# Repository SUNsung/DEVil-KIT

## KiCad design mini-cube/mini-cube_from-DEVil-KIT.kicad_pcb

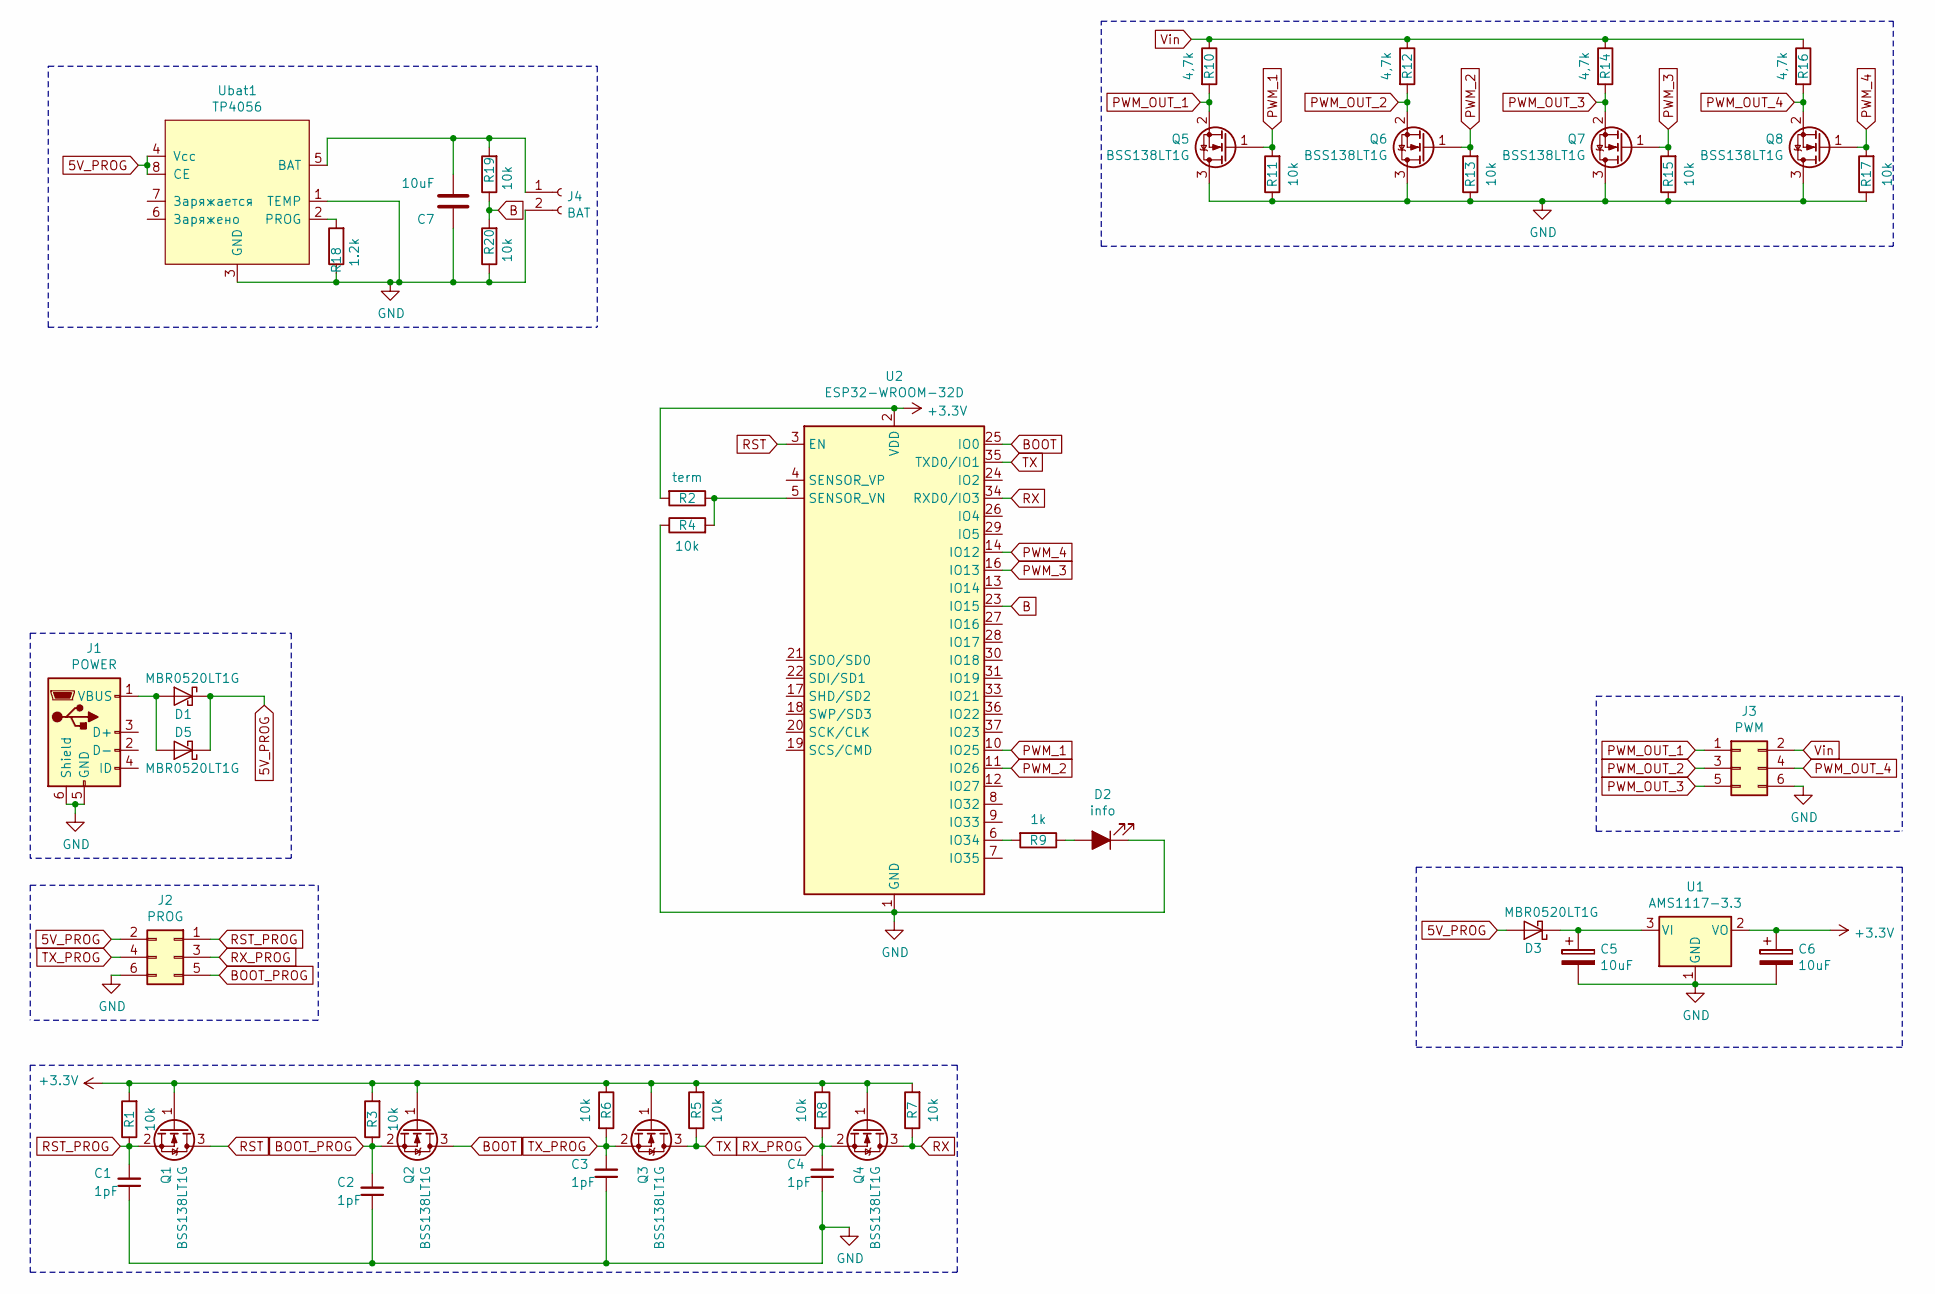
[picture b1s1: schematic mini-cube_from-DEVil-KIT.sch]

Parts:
C1, C2, C3, C4: 1pF; C_0603_1608Metric_Pad1.05x0.95mm_HandSolder
C5, C6: 10uF; CP_EIA-3528-21_Kemet-B_Pad1.50x2.35mm_HandSolder
C7: 10uF; C_0805_2012Metric
D1, D3, D5: MBR0520LT1G; D_SOD-123F
D2: info; D_0805_2012Metric_Castellated
J1: POWER; USB_Mini-B_Lumberg_2486_01_Horizontal
J2: PROG; IDC-Header_2x03_P2.54mm_Horizontal
J3: PWM; IDC-Header_2x03_P2.54mm_Horizontal
J4: BAT; SolderWirePad_1x02_P3.81mm_Drill0.8mm
Q1, Q2, Q3, Q4, Q5, Q6, Q7, Q8: BSS138LT1G; SOT-323_SC-70
R1, R3, R5, R6, R7, R8, R11, R13, R15, R17: 10k; R_0603_1608Metric_Pad1.05x0.95mm_HandSolder
R2: term; R_0805_2012Metric
R4, R19, R20: 10k; R_0805_2012Metric
R9: 1k; R_0805_2012Metric
R10, R12, R14, R16: 4,7k; R_0603_1608Metric_Pad1.05x0.95mm_HandSolder
R18: 1.2k; R_0805_2012Metric
U1: AMS1117-3.3; SOT-223-3_TabPin2
U2: ESP32-WROOM-32D; modul_ESP32S
Ubat1: TP4056; HSOP-8-1EP_3.9x4.9mm_P1.27mm_EP2.41x3.1mm

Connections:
5V_PROG: D1.1 (K), D3.2 (A), D5.1 (K), J2.2, Ubat1.4 (Vcc), Ubat1.8 (CE)
+3V3: C6.1, Q1.1 (G), Q2.1 (G), Q3.1 (G), Q4.1 (G), R1.2, R2.2, R3.2, R5.2, R6.1, R7.2, R8.1, U1.2 (VO), U2.2 (VDD)
B: R19.1, R20.2, U2.23 (IO15)
BOOT: Q2.3 (D), U2.25 (IO0)
BOOT_PROG: C2.2, J2.5, Q2.2 (S), R3.1
GND: C1.1, C2.1, C3.1, C4.1, C5.2, C6.2, C7.2, D2.1 (K), J1.5 (GND), J1.6 (Shield), J2.6, J3.6, J4.2, Q5.3 (D), Q6.3 (D), Q7.3 (D), Q8.3 (D), R4.1, R11.1, R13.1, R15.1, R17.1, R18.1, R20.1, U1.1 (GND), U2.1 (GND), U2.15 (GND), U2.38 (GND), Ubat1.1 (TEMP), Ubat1.3 (GND)
unnamed: C5.1, D3.1 (K), U1.3 (VI)
unnamed: C7.1, J4.1, R19.2, Ubat1.5 (BAT)
unnamed: D1.2 (A), D5.2 (A), J1.1 (VBUS)
unnamed: D2.2 (A), R9.1
unnamed: R2.1, R4.2, U2.5 (SENSOR_VN)
unnamed: R9.2, U2.6 (IO34)
unnamed: R18.2, Ubat1.2 (PROG)
PWM_1: Q5.1 (G), R11.2, U2.10 (IO25)
PWM_2: Q6.1 (G), R13.2, U2.11 (IO26)
PWM_3: Q7.1 (G), R15.2, U2.16 (IO13)
PWM_4: Q8.1 (G), R17.2, U2.14 (IO12)
PWM_OUT_1: J3.1, Q5.2 (S), R10.2
PWM_OUT_2: J3.3, Q6.2 (S), R12.2
PWM_OUT_3: J3.5, Q7.2 (S), R14.2
PWM_OUT_4: J3.4, Q8.2 (S), R16.2
RST: Q1.3 (D), U2.3 (EN)
RST_PROG: C1.2, J2.1, Q1.2 (S), R1.1
RX: Q4.3 (D), R7.1, U2.34 (RXD0/IO3)
RX_PROG: C4.2, J2.3, Q4.2 (S), R8.2
TX: Q3.3 (D), R5.1, U2.35 (TXD0/IO1)
TX_PROG: C3.2, J2.4, Q3.2 (S), R6.2
Vin: J3.2, R10.1, R12.1, R14.1, R16.1

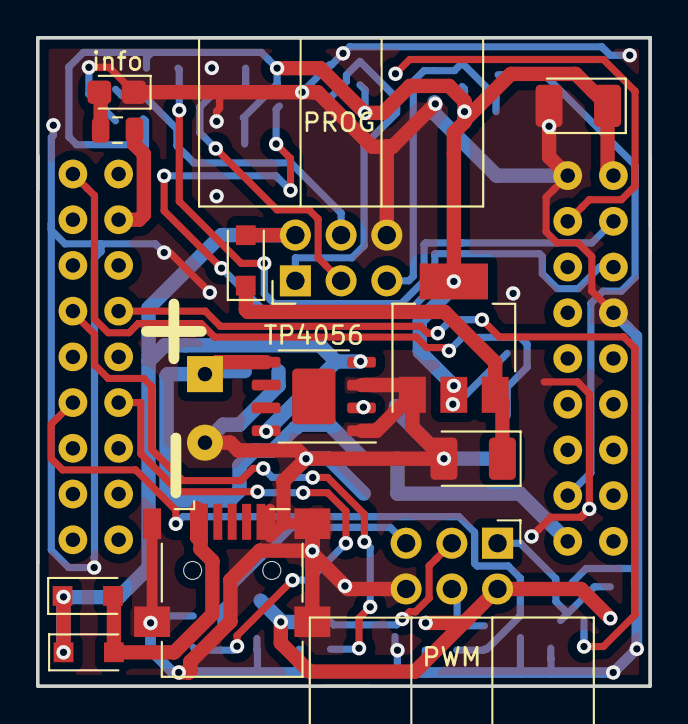
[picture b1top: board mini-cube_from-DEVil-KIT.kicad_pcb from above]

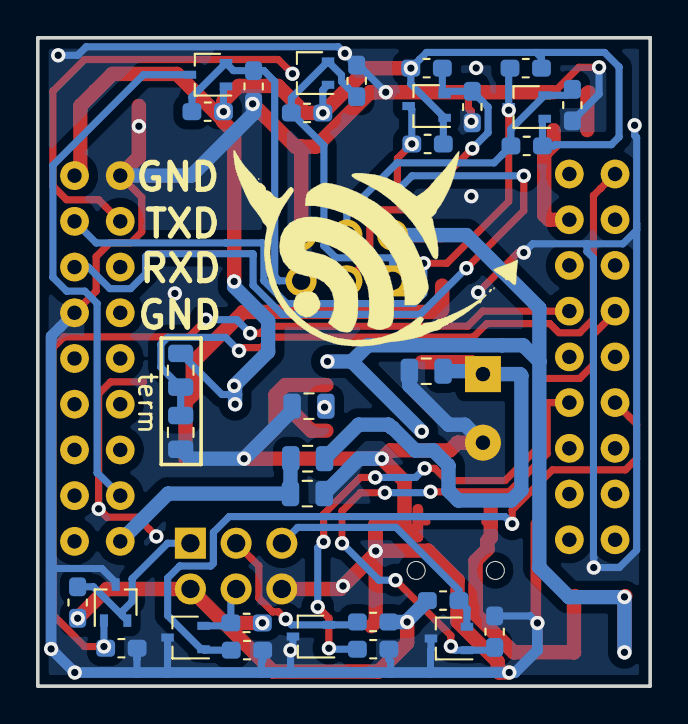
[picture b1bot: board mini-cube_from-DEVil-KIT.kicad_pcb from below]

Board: 2 copper layers, 34.0 x 36.0 mm, 46 parts (33 on the bottom side), 28 nets.

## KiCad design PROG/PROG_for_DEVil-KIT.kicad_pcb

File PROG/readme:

The module programmer is worn on the USB-UART CP2104 CP2102 adapter

6\май\2019 - Собрал. Нежизнеспособно. Зашита пробивается на раз. Греется как утюг. Резюмируя - при необходимости программатор собирать с нуля под задачу.

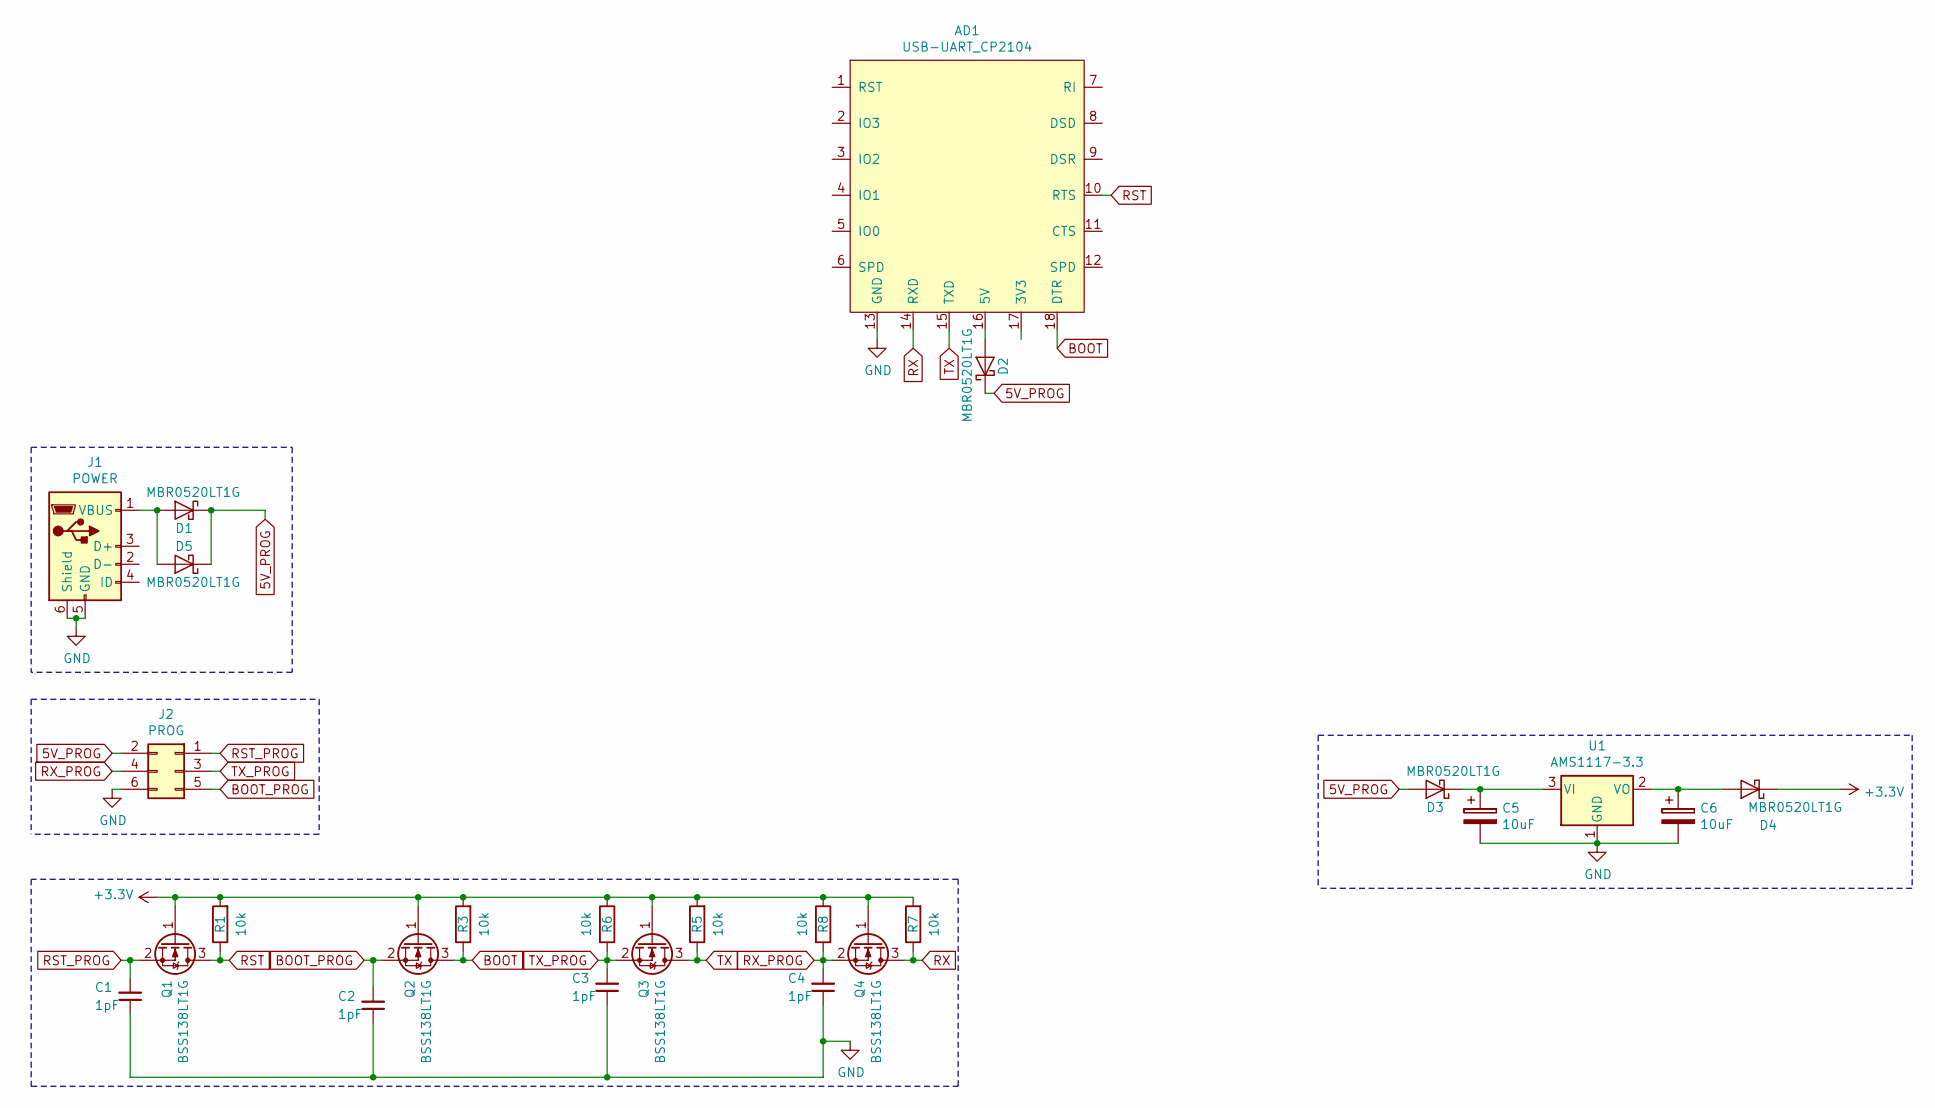
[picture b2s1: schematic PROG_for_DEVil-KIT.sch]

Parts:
AD1: USB-UART_CP2104
C1, C2, C3, C4: 1pF; C_0603_1608Metric_Pad1.05x0.95mm_HandSolder
C5, C6: 10uF; CP_EIA-3528-21_Kemet-B_Pad1.50x2.35mm_HandSolder
D1, D2, D3, D4, D5: MBR0520LT1G; D_SOD-123F
J1: POWER; USB_Mini-B_Lumberg_2486_01_Horizontal
J2: PROG; IDC-Header_2x03_P2.54mm_Vertical
Q1, Q2, Q3, Q4: BSS138LT1G; SOT-323_SC-70
R1, R3, R5, R6, R7, R8: 10k; R_0603_1608Metric_Pad1.05x0.95mm_HandSolder
U1: AMS1117-3.3; SOT-223-3_TabPin2

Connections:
5V_PROG: D1.1 (K), D2.1 (K), D3.2 (A), D5.1 (K), J2.2
+3V3: D4.1 (K), Q1.1 (G), Q2.1 (G), Q3.1 (G), Q4.1 (G), R1.2, R3.2, R5.2, R6.1, R7.2, R8.1
BOOT: AD1.18 (DTR), Q2.3 (D), R3.1
BOOT_PROG: C2.2, J2.5, Q2.2 (S)
GND: AD1.13 (GND), C1.1, C2.1, C3.1, C4.1, C5.2, C6.2, J1.5 (GND), J1.6 (Shield), J2.6, U1.1 (GND)
unnamed: AD1.16 (5V), D2.2 (A)
unnamed: C5.1, D3.1 (K), U1.3 (VI)
unnamed: C6.1, D4.2 (A), U1.2 (VO)
unnamed: D1.2 (A), D5.2 (A), J1.1 (VBUS)
RST: AD1.10 (RTS), Q1.3 (D), R1.1
RST_PROG: C1.2, J2.1, Q1.2 (S)
RX: AD1.14 (RXD), Q4.3 (D), R7.1
RX_PROG: C4.2, J2.4, Q4.2 (S), R8.2
TX: AD1.15 (TXD), Q3.3 (D), R5.1
TX_PROG: C3.2, J2.3, Q3.2 (S), R6.2

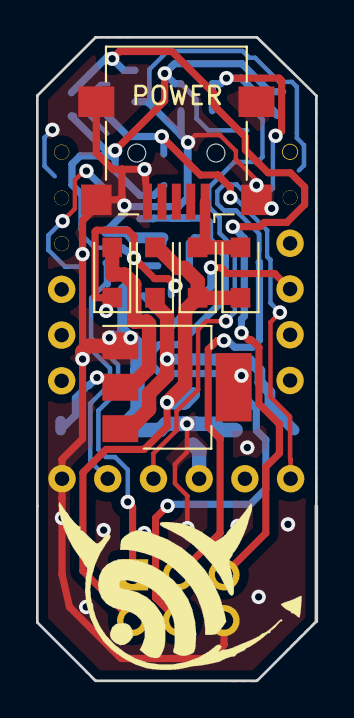
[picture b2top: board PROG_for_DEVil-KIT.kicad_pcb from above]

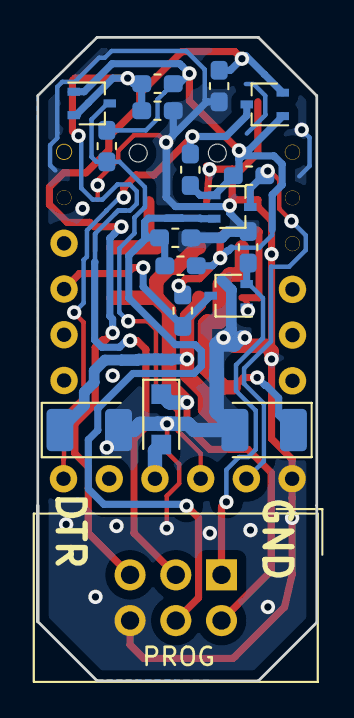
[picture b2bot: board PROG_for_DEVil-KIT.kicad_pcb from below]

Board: 2 copper layers, 15.5 x 35.7 mm, 25 parts (18 on the bottom side), 15 nets.

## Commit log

2019-04-23 logo
2019-04-23 Create mini-cube
